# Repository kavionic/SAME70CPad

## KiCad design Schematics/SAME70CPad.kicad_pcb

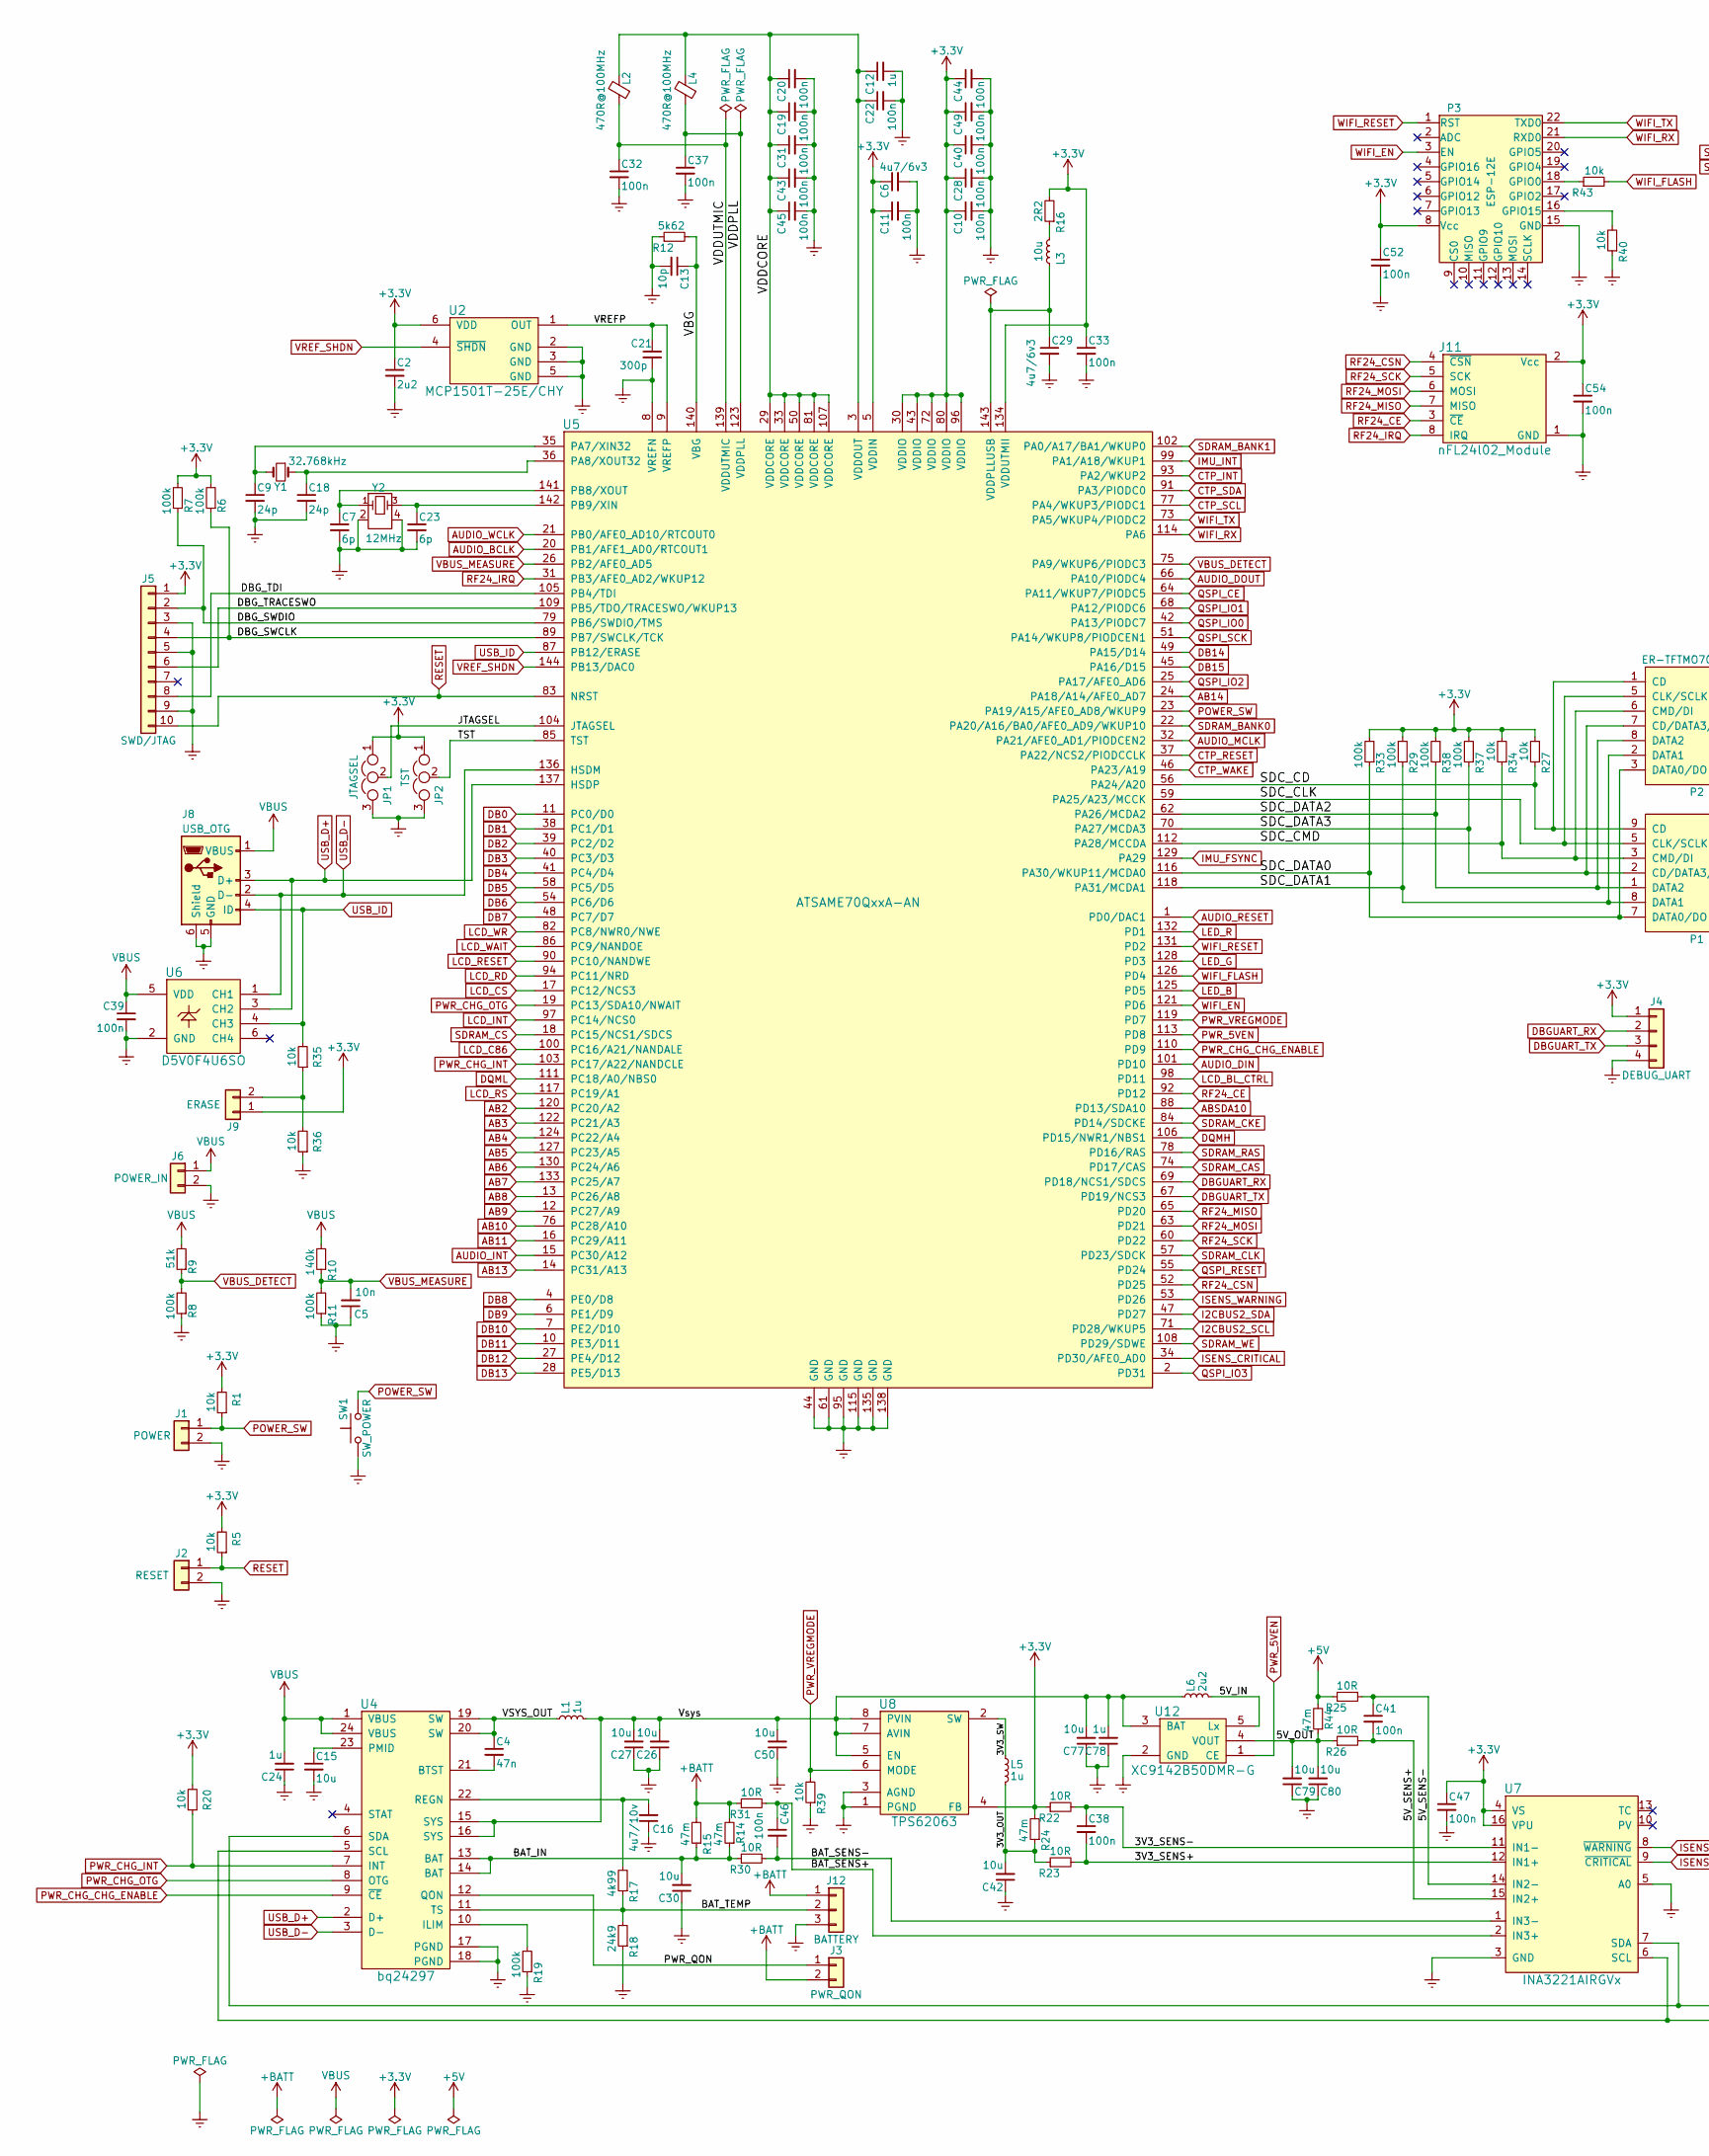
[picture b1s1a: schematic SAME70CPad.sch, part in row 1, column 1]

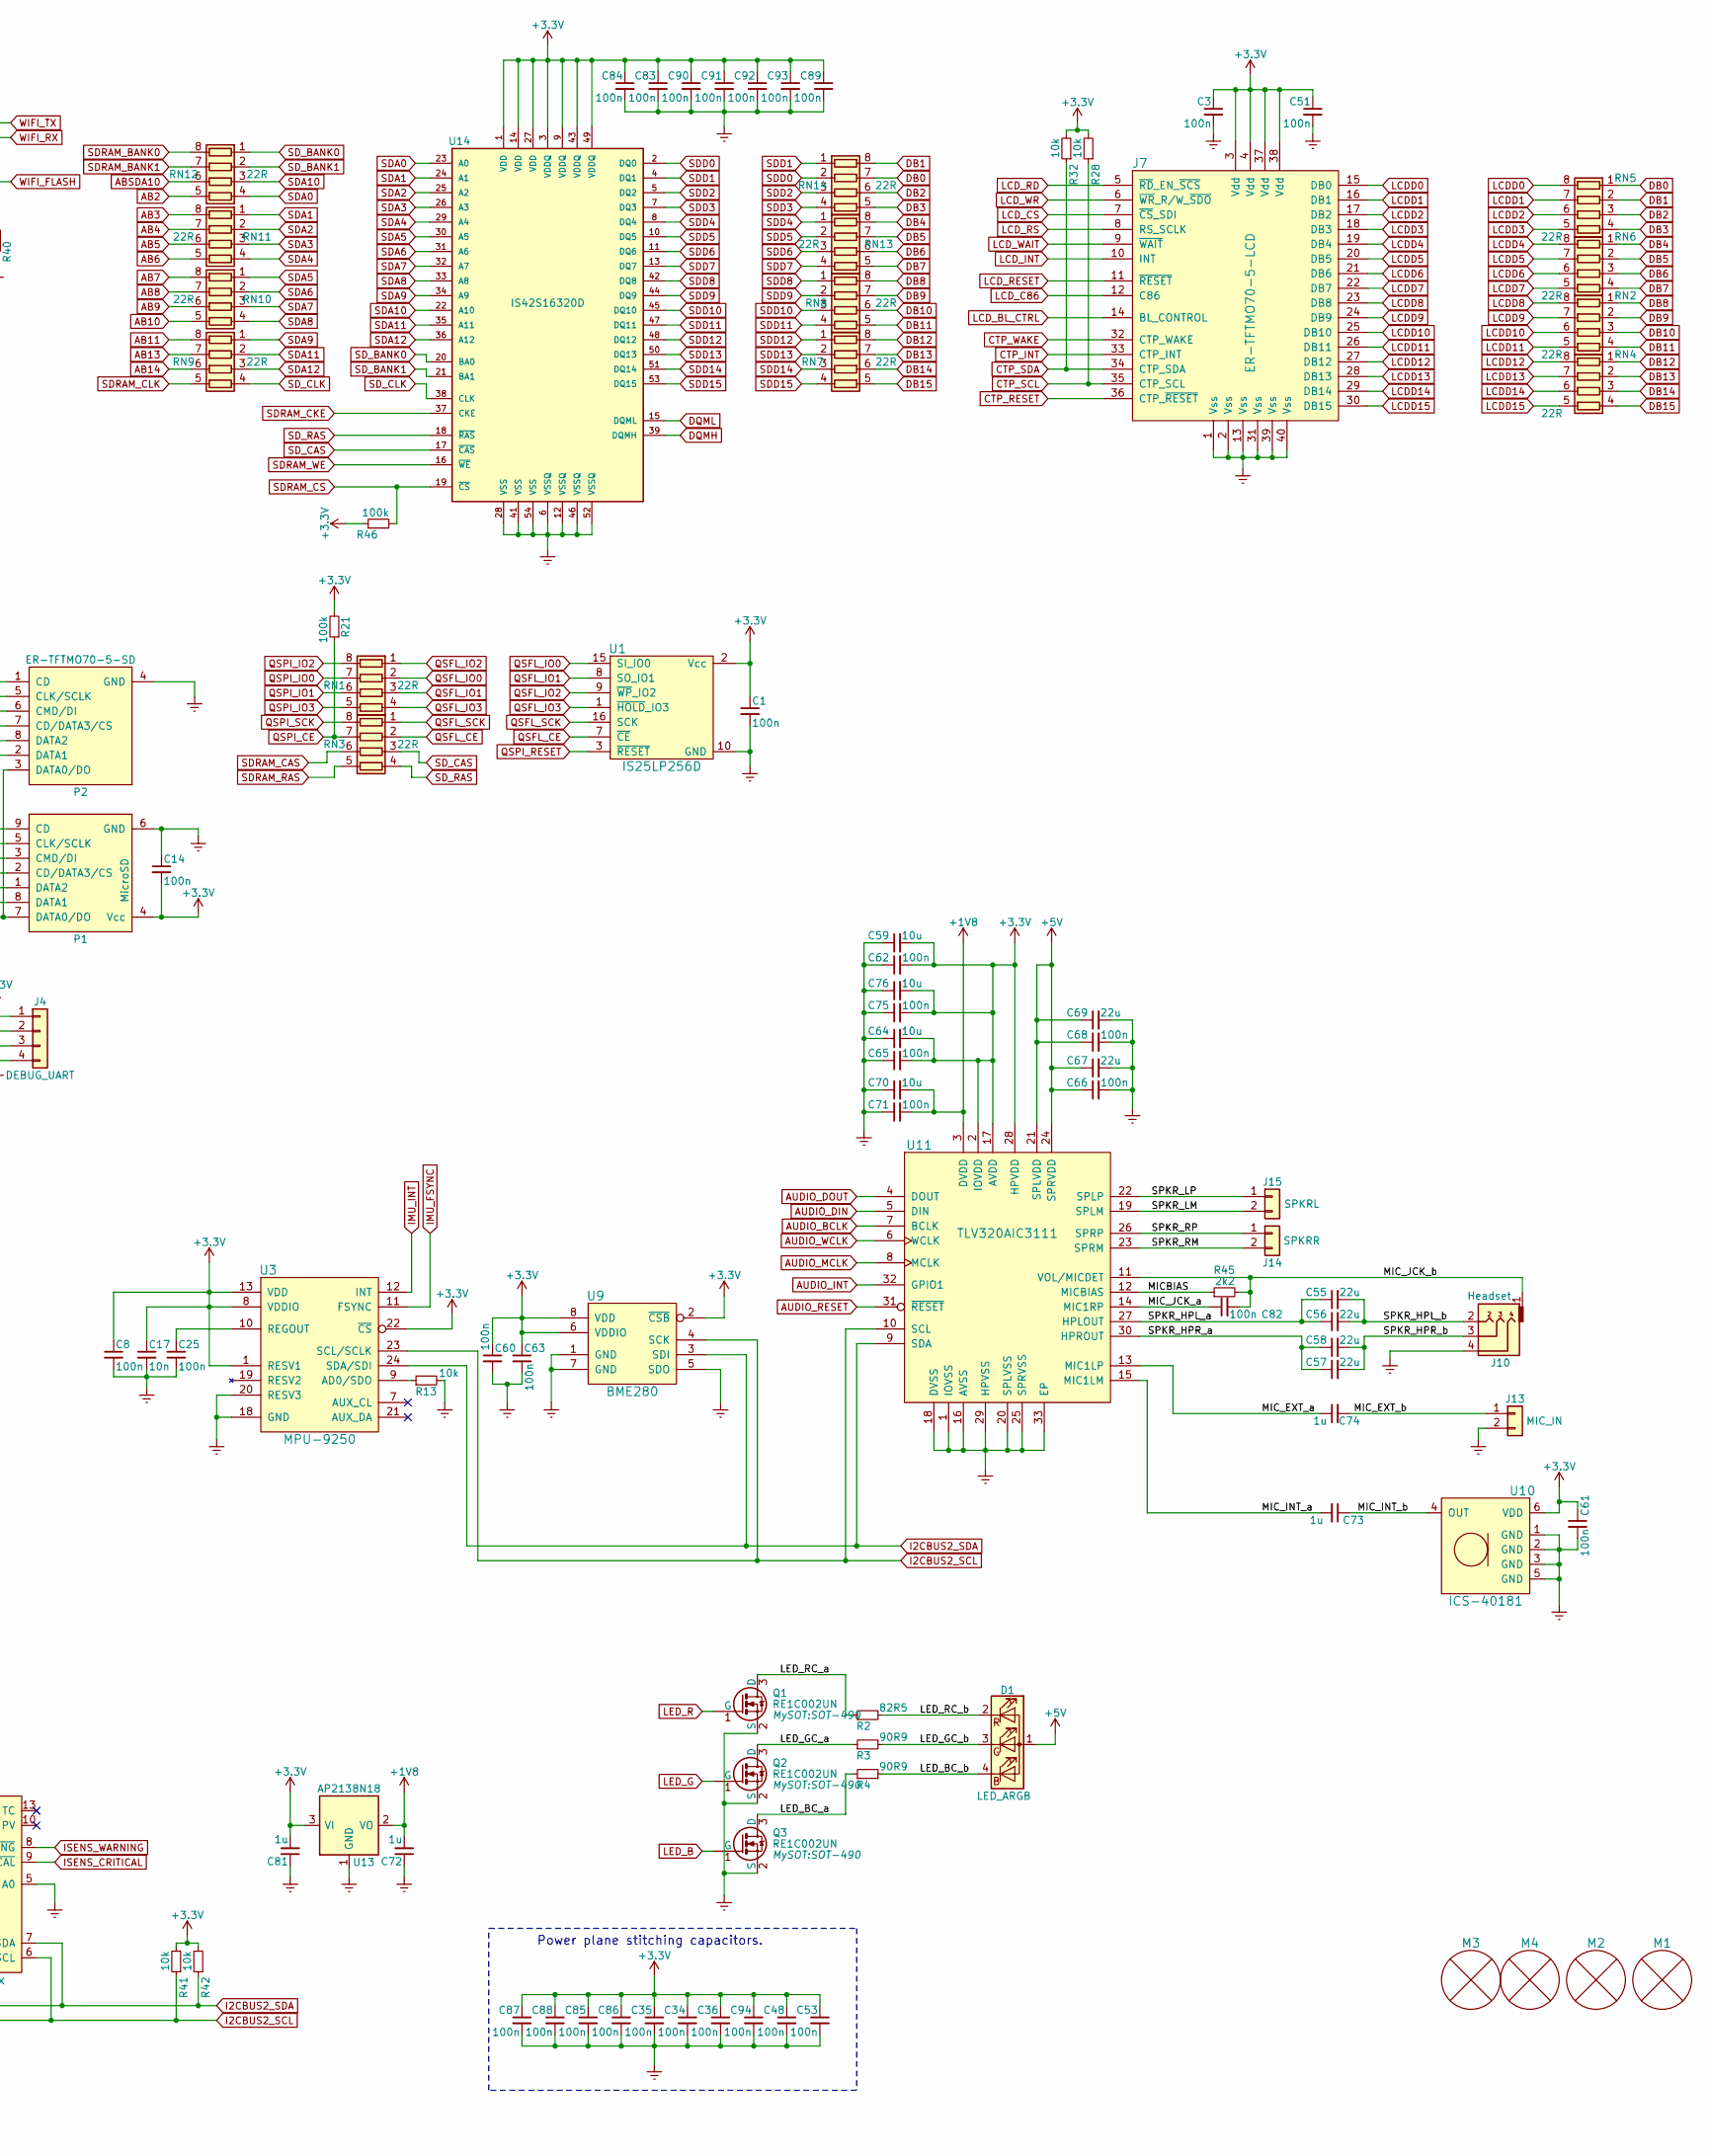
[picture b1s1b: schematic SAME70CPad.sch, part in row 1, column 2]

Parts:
C1, C3, C8, C10, C11, C14, C19, C20, C22, C25, C28, C31, C32, C33, C34, C35, C36, C37, C38, C39, C40, C41, C43, C44, C45, C46, C47, C48, C49, C51, C52, C53, C54, C60, C61, C62, C63, C65, C66, C68, C71, C75, C82, C83, C84, C85, C86, C87, C88, C89, C90, C91, C92, C93, C94: 100n; C_0603
C2: 2u2; C_0603
C4: 47n; C_0603
C5, C17: 10n; C_0603
C6, C29: 4u7/6v3; C_0603
C7, C23: 6p; C_0603
C9, C18: 24p; C_0603
C12, C24, C72, C73, C74, C78, C81: 1u; C_0603
C13: 10p; C_0603
C15, C26, C27, C30, C42, C50, C59, C64, C70, C76, C77, C79, C80: 10u; C_0805
C16: 4u7/10v; C_0805
C21: 300p; C_0603
C55, C56, C57, C58, C67, C69: 22u; C_1206
D1: LED_ARGB; PLCC4_3228
J1: POWER; JST_ZH_S2B-ZR_02x1.50mm_Angled
J2: RESET; JST_ZH_S2B-ZR_02x1.50mm_Angled
J3: PWR_QON; JST_ZH_S2B-ZR_02x1.50mm_Angled
J4: DEBUG_UART; JST_ZH_S4B-ZR_04x1.50mm_Angled
J5: SWD/JTAG; BoxHeader_Straight_2x05_Pitch1.27mm
J6: POWER_IN; JST_EH_S02B-EH_02x2.50mm_Angled
J7: ER-TFTMO70-5-LCD; ER-CON40HB-2
J8: USB_OTG; USB_Micro-B_Molex-105017-0001
J9: ERASE; PinHeader_1x02
J10: Headset; SJ2-3514A-SMT
J11: nFL24l02_Module; nFL24l02_module
J12: BATTERY; JST_EH_S03B-EH_03x2.50mm_Angled
J13: MIC_IN; JST_ZH_S2B-ZR_02x1.50mm_Angled
J14: SPKRL; JST_ZH_S2B-ZR_02x1.50mm_Angled
J15: SPKRR; JST_ZH_S2B-ZR_02x1.50mm_Angled
JP1: JTAGSEL; PinHeader_1x03
JP2: TST; PinHeader_1x03
L1, L5: 1u; L_2020
L2, L4: 470R@100MHz; Choke_SMD_0603_Standard
L3: 10u; L_0805
L6: 2u2; L_2020
M1, M2, M3, M4: MountingHole; MH7x3
P1: MicroSD
P2: ER-TFTMO70-5-SD; ER-CON08HB-2
P3: ESP-12E
Q1, Q2, Q3: RE1C002UN; SOT-490
R1, R5, R13, R20, R27, R28, R32, R34, R35, R36, R39, R40, R41, R42, R43: 10k; R_0603
R2: 82R5; R_0603
R3, R4: 90R9; R_0603
R6, R7, R8, R11, R19, R21, R29, R33, R37, R38, R46: 100k; R_0603
R9: 51k; R_0603
R10: 140k; R_0603
R12: 5k62; R_0603
R14, R15, R24, R44: 47m; R_0603
R16: 2R2; R_0603
R17: 4k99; R_0603
R18: 24k9; R_0603
R22, R23, R25, R26, R30, R31: 10R; R_0603
R45: 2k2; R_0603
RN1, RN2, RN3, RN4, RN5, RN6, RN7, RN8, RN9, RN10, RN11, RN12, RN13, RN14: 22R; R_0402x4
SW1: SW_POWER; TactSwitch_TH_RightAngle_6.3x7.5x7.1mm_5.85mm
U1: IS25LP256D; SOIC-16_7.5x10.3mm_Pitch1.27mm
U2: MCP1501T-25E/CHY; SOT-23-6
U3: MPU-9250; QFN-24_3x3mm_Pitch0.4mm
U4: bq24297; QFN-24-1EP_4x4mm_Pitch0.5mm
U5: ATSAME70QxxA-AN; TQFP-144_20x20mm_Pitch0.5mm
U6: D5V0F4U6SO; SOT-23-6
U7: INA3221AIRGVx; QFN-16-1EP_4x4mm_Pitch0.65mm
U8: TPS62063; WSON-8_0.5mm_Pitch
U9: BME280
U10: ICS-40181
U11: TLV320AIC3111; QFN-32-1EP_5x5mm_Pitch0.5mm
U12: XC9142B50DMR-G; SOT-25
U13: AP2138N18; SOT-23
U14: IS42S16320D; TSOP-54
Y1: 32.768kHz; Crystal_SMD_3215-2pin_3.2x1.5mm
Y2: 12MHz; Crystal-5032

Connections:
+1V8: C70.2, C71.2, C72.2, U11.3 (DVDD), U13.2 (VO)
+3V3: C1.1, C2.1, C3.1, C6.1, C8.1, C10.1, C11.1, C14.2, C17.1, C28.1, C33.1, C34.1, C35.1, C36.1, C40.1, C44.1, C47.1, C48.1, C49.1, C51.1, C52.1, C53.1, C54.1, C59.2, C60.1, C61.1, C62.2, C63.1, C64.2, C65.2, C75.2, C76.2, C81.2, C83.1, C84.1, C85.1, C86.1, C87.1, C88.1, C89.1, C90.1, C91.1, C92.1, C93.1, C94.1, J4.1, J5.1, J7.3 (Vdd), J7.4 (Vdd), J7.37 (Vdd), J7.38 (Vdd), J9.1, J11.2 (Vcc), JP1.1, JP2.1, P1.4 (Vcc), P3.8 (Vcc), R1.2, R5.2, R6.2, R7.2, R16.2, R20.2, R21.2, R22.1, R24.2, R27.2, R28.2, R29.2, R32.2, R33.2, R34.2, R37.2, R38.2, R41.2, R42.2, R46.1, U1.2 (Vcc), U2.6 (VDD), U3.1 (RESV1), U3.8 (VDDIO), U3.13 (VDD), U3.22 (~CS), U5.5 (VDDIN), U5.30 (VDDIO), U5.43 (VDDIO), U5.72 (VDDIO), U5.80 (VDDIO), U5.96 (VDDIO), U5.134 (VDDUTMII), U7.4 (VS), U7.16 (VPU), U8.4 (FB), U9.2 (~CSB), U9.6 (VDDIO), U9.8 (VDD), U10.6 (VDD), U11.2 (IOVDD), U11.17 (AVDD), U11.28 (HPVDD), U13.3 (VI), U14.1 (VDD), U14.3 (VDDQ), U14.9 (VDDQ), U14.14 (VDD), U14.27 (VDD), U14.43 (VDDQ), U14.49 (VDDQ)
+5V: C66.1, C67.1, C68.1, C69.1, D1.1 (A), R25.1, R44.2, U11.21 (SPLVDD), U11.24 (SPRVDD)
+BATT: J3.2, J12.1, R14.2, R15.2, R31.1
/3V3_OUT: C42.2, L5.2, R23.1, R24.1
/3V3_SENS+: C38.2, R23.2, U7.12 (IN1+)
/3V3_SENS-: C38.1, R22.2, U7.11 (IN1-)
/3V3_SW: L5.1, U8.2 (SW)
/5V_IN: L6.2, U12.5 (Lx)
/5V_OUT: C79.2, C80.2, R26.1, R44.1, U12.4 (VOUT)
/5V_SENS+: C41.2, R26.2, U7.15 (IN2+)
/5V_SENS-: C41.1, R25.2, U7.14 (IN2-)
/BAT_IN: C30.2, R14.1, R15.1, R30.1, U4.13 (BAT), U4.14 (BAT)
/BAT_SENS+: C46.1, R31.2, U7.2 (IN3+)
/BAT_SENS-: C46.2, R30.2, U7.1 (IN3-)
/BAT_TEMP: J12.2, R17.1, R18.2, U4.11 (TS)
/DBG_SWCLK: J5.4, R6.1, U5.89 (PB7/SWCLK/TCK)
/DBG_SWDIO: J5.2, R7.1, U5.79 (PB6/SWDIO/TMS)
/DBG_TDI: J5.8, U5.105 (PB4/TDI)
/DBG_TRACESWO: J5.6, U5.109 (PB5/TDO/TRACESWO/WKUP13)
/JTAGSEL: JP1.2, U5.104 (JTAGSEL)
/LED_BC_a: Q3.3 (D), R4.1
/LED_BC_b: D1.4 (BK), R4.2
/LED_GC_a: Q2.3 (D), R3.1
/LED_GC_b: D1.3 (GK), R3.2
/LED_RC_a: Q1.3 (D), R2.1
/LED_RC_b: D1.2 (RK), R2.2
/MICBIAS: R45.1, U11.12 (MICBIAS)
/MIC_EXT_a: C74.1, U11.13 (MIC1LP)
/MIC_EXT_b: C74.2, J13.1
/MIC_INT_a: C73.2, U11.15 (MIC1LM)
/MIC_INT_b: C73.1, U10.4 (OUT)
/MIC_JCK_a: C82.1, U11.14 (MIC1RP)
/MIC_JCK_b: C82.2, J10.1, R45.2, U11.11 (VOL/MICDET)
/PWR_QON: J3.1, U4.12 (QON)
/SDC_CD: P1.9 (CD), P2.1 (CD), R27.1, U5.56 (PA24/A20)
/SDC_CLK: P1.5 (CLK/SCLK), P2.5 (CLK/SCLK), U5.59 (PA25/A23/MCCK)
/SDC_CMD: P1.3 (CMD/DI), P2.6 (CMD/DI), R34.1, U5.112 (PA28/MCCDA)
/SDC_DATA0: P1.7 (DATA0/DO), P2.3 (DATA0/DO), R33.1, U5.116 (PA30/WKUP11/MCDA0)
/SDC_DATA1: P1.8 (DATA1), P2.2 (DATA1), R29.1, U5.118 (PA31/MCDA1)
/SDC_DATA2: P1.1 (DATA2), P2.8 (DATA2), R38.1, U5.62 (PA26/MCDA2)
/SDC_DATA3: P1.2 (CD/DATA3/CS), P2.7 (CD/DATA3/CS), R37.1, U5.70 (PA27/MCDA3)
/SPKR_HPL_a: C55.1, C56.1, U11.27 (HPLOUT)
/SPKR_HPL_b: C55.2, C56.2, J10.2
/SPKR_HPR_a: C57.1, C58.1, U11.30 (HPROUT)
/SPKR_HPR_b: C57.2, C58.2, J10.3
/SPKR_LM: J14.2, U11.19 (SPLM)
/SPKR_LP: J14.1, U11.22 (SPLP)
/SPKR_RM: J15.2, U11.23 (SPRM)
/SPKR_RP: J15.1, U11.26 (SPRP)
/TST: JP2.2, U5.85 (TST)
/VBG: C13.1, R12.2, U5.140 (VBG)
/VDDCORE: C12.1, C19.1, C20.1, C22.1, C31.1, C43.1, C45.1, L2.2, L4.2, U5.3 (VDDOUT), U5.29 (VDDCORE), U5.33 (VDDCORE), U5.50 (VDDCORE), U5.81 (VDDCORE), U5.107 (VDDCORE)
/VDDPLL: C37.1, L4.1, U5.123 (VDDPLL)
/VDDUTMIC: C32.1, L2.1, U5.139 (VDDUTMIC)
/VREFP: C21.1, U2.1 (OUT), U5.9 (VREFP)
/VSYS_OUT: C4.1, L1.1, U4.19 (SW), U4.20 (SW)
/Vsys: C26.2, C27.2, C50.2, C77.2, C78.2, L1.2, L6.1, U4.15 (SYS), U4.16 (SYS), U8.5 (EN), U8.7 (AVIN), U8.8 (PVIN), U12.3 (BAT)
AB2: RN12.5 (R4.2), U5.120 (PC20/A2)
AB3: RN11.8 (R1.2), U5.122 (PC21/A3)
AB4: RN11.7 (R2.2), U5.124 (PC22/A4)
AB5: RN11.6 (R3.2), U5.127 (PC23/A5)
AB6: RN11.5 (R4.2), U5.130 (PC24/A6)
AB7: RN10.8 (R1.2), U5.133 (PC25/A7)
AB8: RN10.7 (R2.2), U5.13 (PC26/A8)
AB9: RN10.6 (R3.2), U5.12 (PC27/A9)
AB10: RN10.5 (R4.2), U5.76 (PC28/A10)
AB11: RN9.8 (R1.2), U5.16 (PC29/A11)
AB13: RN9.7 (R2.2), U5.14 (PC31/A13)
AB14: RN9.6 (R3.2), U5.24 (PA18/A14/AFE0_AD7)
ABSDA10: RN12.6 (R3.2), U5.88 (PD13/SDA10)
AUDIO_BCLK: U5.20 (PB1/AFE1_AD0/RTCOUT1), U11.7 (BCLK)
AUDIO_DIN: U5.101 (PD10), U11.5 (DIN)
AUDIO_DOUT: U5.66 (PA10/PIODC4), U11.4 (DOUT)
AUDIO_INT: U5.15 (PC30/A12), U11.32 (GPIO1)
AUDIO_MCLK: U5.32 (PA21/AFE0_AD1/PIODCEN2), U11.8 (MCLK)
AUDIO_RESET: U5.1 (PD0/DAC1), U11.31 (~RESET)
AUDIO_WCLK: U5.21 (PB0/AFE0_AD10/RTCOUT0), U11.6 (WCLK)
CTP_INT: J7.33 (CTP_INT), U5.93 (PA2/WKUP2)
CTP_RESET: J7.36 (CTP_~RESET), U5.37 (PA22/NCS2/PIODCCLK)
CTP_SCL: J7.35 (CTP_SCL), R28.1, U5.77 (PA4/WKUP3/PIODC1)
CTP_SDA: J7.34 (CTP_SDA), R32.1, U5.91 (PA3/PIODC0)
CTP_WAKE: J7.32 (CTP_WAKE), U5.46 (PA23/A19)
DB0: RN5.1 (R1.1), RN14.7 (R2.2), U5.11 (PC0/D0)
DB1: RN5.2 (R2.1), RN14.8 (R1.2), U5.38 (PC1/D1)
DB2: RN5.3 (R3.1), RN14.6 (R3.2), U5.39 (PC2/D2)
DB3: RN5.4 (R4.1), RN14.5 (R4.2), U5.40 (PC3/D3)
DB4: RN6.1 (R1.1), RN13.8 (R1.2), U5.41 (PC4/D4)
DB5: RN6.2 (R2.1), RN13.7 (R2.2), U5.58 (PC5/D5)
DB6: RN6.3 (R3.1), RN13.6 (R3.2), U5.54 (PC6/D6)
DB7: RN6.4 (R4.1), RN13.5 (R4.2), U5.48 (PC7/D7)
DB8: RN2.1 (R1.1), RN8.8 (R1.2), U5.4 (PE0/D8)
DB9: RN2.2 (R2.1), RN8.7 (R2.2), U5.6 (PE1/D9)
DB10: RN2.3 (R3.1), RN8.6 (R3.2), U5.7 (PE2/D10)
DB11: RN2.4 (R4.1), RN8.5 (R4.2), U5.10 (PE3/D11)
DB12: RN4.1 (R1.1), RN7.8 (R1.2), U5.27 (PE4/D12)
DB13: RN4.2 (R2.1), RN7.7 (R2.2), U5.28 (PE5/D13)
DB14: RN4.3 (R3.1), RN7.6 (R3.2), U5.49 (PA15/D14)
DB15: RN4.4 (R4.1), RN7.5 (R4.2), U5.45 (PA16/D15)
DBGUART_RX: J4.2, U5.69 (PD18/NCS1/SDCS)
DBGUART_TX: J4.3, U5.67 (PD19/NCS3)
DQMH: U5.106 (PD15/NWR1/NBS1), U14.39 (DQMH)
DQML: U5.111 (PC18/A0/NBS0), U14.15 (DQML)
Earth: C1.2, C2.2, C3.2, C5.1, C6.2, C7.2, C8.2, C9.2, C10.2, C11.2, C12.2, C13.2, C14.1, C15.2, C16.1, C17.2, C18.2, C19.2, C20.2, C21.2, C22.2, C23.2, C24.1, C25.2, C26.1, C27.1, C28.2, C29.2, C30.1, C31.2, C32.2, C33.2, C34.2, C35.2, C36.2, C37.2, C39.2, C40.2, C42.1, C43.2, C44.2, C45.2, C47.2, C48.2, C49.2, C50.1, C51.2, C52.2, C53.2, C54.2, C59.1, C60.2, C61.2, C62.1, C63.2, C64.1, C65.1, C66.2, C67.2, C68.2, C69.2, C70.1, C71.1, C72.1, C75.1, C76.1, C77.1, C78.1, C79.1, C80.1, C81.1, C83.2, C84.2, C85.2, C86.2, C87.2, C88.2, C89.2, C90.2, C91.2, C92.2, C93.2, C94.2, J1.2, J2.2, J4.4, J5.3, J5.5, J5.9, J6.2, J7.1 (Vss), J7.2 (Vss), J7.13 (Vss), J7.31 (Vss), J7.39 (Vss), J7.40 (Vss), J8.5 (GND), J8.6 (Shield), J10.4, J11.1 (GND), J12.3, J13.2, JP1.3, JP2.3, P1.6 (GND), P1.10 (GND), P1.11 (GND), P1.12 (GND), P1.13 (GND), P2.4 (GND), P3.15 (GND), Q1.2 (S), Q2.2 (S), Q3.2 (S), R8.1, R11.1, R12.1, R13.2, R18.1, R19.1, R36.1, R39.1, R40.1, SW1.1, U1.10 (GND), U2.2 (GND), U2.3 (GND), U2.5 (GND), U3.18 (GND), U3.20 (RESV3), U4.17 (PGND), U4.18 (PGND), U4.25 (PGND), U5.8 (VREFN), U5.44 (GND), U5.61 (GND), U5.95 (GND), U5.115 (GND), U5.135 (GND), U5.138 (GND), U6.2 (GND), U7.3 (GND), U7.5 (A0), U7.17 (GND), U8.1 (PGND), U8.3 (AGND), U8.9 (PGND), U9.1 (GND), U9.5 (SDO), U9.7 (GND), U10.1 (GND), U10.2 (GND), U10.3 (GND), U10.5 (GND), U11.1 (IOVSS), U11.16 (AVSS), U11.18 (DVSS), U11.20 (SPLVSS), U11.25 (SPRVSS), U11.29 (HPVSS), U11.33 (EP), U12.2 (GND), U13.1 (GND), U14.6 (VSSQ), U14.12 (VSSQ), U14.28 (VSS), U14.41 (VSS), U14.46 (VSSQ), U14.52 (VSSQ), U14.54 (VSS), Y2.2 (NC), Y2.4 (NC)
I2CBUS2_SCL: R41.1, U3.23 (SCL/SCLK), U4.5 (SCL), U5.71 (PD28/WKUP5), U7.6 (SCL), U9.4 (SCK), U11.10 (SCL)
I2CBUS2_SDA: R42.1, U3.24 (SDA/SDI), U4.6 (SDA), U5.47 (PD27), U7.7 (SDA), U9.3 (SDI), U11.9 (SDA)
IMU_FSYNC: U3.11 (FSYNC), U5.129 (PA29)
IMU_INT: U3.12 (INT), U5.99 (PA1/A18/WKUP1)
ISENS_CRITICAL: U5.34 (PD30/AFE0_AD0), U7.9 (~CRITICAL)
ISENS_WARNING: U5.53 (PD26), U7.8 (~WARNING)
LCDD0: J7.15 (DB0), RN5.8 (R1.2)
LCDD1: J7.16 (DB1), RN5.7 (R2.2)
LCDD2: J7.17 (DB2), RN5.6 (R3.2)
LCDD3: J7.18 (DB3), RN5.5 (R4.2)
LCDD4: J7.19 (DB4), RN6.8 (R1.2)
LCDD5: J7.20 (DB5), RN6.7 (R2.2)
LCDD6: J7.21 (DB6), RN6.6 (R3.2)
LCDD7: J7.22 (DB7), RN6.5 (R4.2)
LCDD8: J7.23 (DB8), RN2.8 (R1.2)
LCDD9: J7.24 (DB9), RN2.7 (R2.2)
LCDD10: J7.25 (DB10), RN2.6 (R3.2)
LCDD11: J7.26 (DB11), RN2.5 (R4.2)
LCDD12: J7.27 (DB12), RN4.8 (R1.2)
LCDD13: J7.28 (DB13), RN4.7 (R2.2)
LCDD14: J7.29 (DB14), RN4.6 (R3.2)
LCDD15: J7.30 (DB15), RN4.5 (R4.2)
LCD_BL_CTRL: J7.14 (BL_CONTROL), U5.98 (PD11)
LCD_C86: J7.12 (C86), U5.100 (PC16/A21/NANDALE)
LCD_CS: J7.7 (~CS~_SDI), U5.17 (PC12/NCS3)
LCD_INT: J7.10 (INT), U5.97 (PC14/NCS0)
LCD_RD: J7.5 (~RD~_EN_~SCS), U5.94 (PC11/NRD)
LCD_RESET: J7.11 (~RESET), U5.90 (PC10/NANDWE)
LCD_RS: J7.8 (RS_SCLK), U5.117 (PC19/A1)
LCD_WAIT: J7.9 (~WAIT), U5.86 (PC9/NANDOE)
LCD_WR: J7.6 (~WR~_R/W_~SDO), U5.82 (PC8/NWR0/NWE)
LED_B: Q3.1 (G), U5.125 (PD5)
LED_G: Q2.1 (G), U5.128 (PD3)
LED_R: Q1.1 (G), U5.132 (PD1)
unnamed: C4.2, U4.21 (BTST)
unnamed: C7.1, U5.141 (PB8/XOUT), Y2.1 (X1)
unnamed: C9.1, U5.35 (PA7/XIN32), Y1.2
unnamed: C15.1, U4.23 (PMID)
unnamed: C16.2, R17.2, U4.22 (REGN)
unnamed: C18.1, U5.36 (PA8/XOUT32), Y1.1
unnamed: C23.1, U5.142 (PB9/XIN), Y2.3 (X2)
unnamed: C25.1, U3.10 (REGOUT)
unnamed: C29.1, L3.1, U5.143 (VDDPLLUSB)
unnamed: J9.2, R35.1, R36.2
unnamed: L3.2, R16.1
unnamed: P3.16 (GPIO15), R40.2
unnamed: P3.18 (GPIO0), R43.1
unnamed: R13.1, U3.9 (AD0/SDO)
unnamed: R19.2, U4.10 (ILIM)
POWER_SW: J1.1, R1.1, SW1.2, U5.23 (PA19/A15/AFE0_AD8/WKUP9)
PWR_5VEN: U5.113 (PD8), U12.1 (CE)
PWR_CHG_CHG_ENABLE: U4.9 (~CE), U5.110 (PD9)
PWR_CHG_INT: R20.1, U4.7 (INT), U5.103 (PC17/A22/NANDCLE)
PWR_CHG_OTG: U4.8 (OTG), U5.19 (PC13/SDA10/NWAIT)
PWR_VREGMODE: R39.2, U5.119 (PD7), U8.6 (MODE)
QSFL_CE: RN3.2 (R2.1), U1.7 (~CE)
QSFL_IO0: RN1.2 (R2.1), U1.15 (SI_IO0)
QSFL_IO1: RN1.3 (R3.1), U1.8 (SO_IO1)
QSFL_IO2: RN1.1 (R1.1), U1.9 (~WP~_IO2)
QSFL_IO3: RN1.4 (R4.1), U1.1 (~HOLD~_IO3)
QSFL_SCK: RN3.1 (R1.1), U1.16 (SCK)
QSPI_CE: R21.1, RN3.7 (R2.2), U5.64 (PA11/WKUP7/PIODC5)
QSPI_IO0: RN1.7 (R2.2), U5.42 (PA13/PIODC7)
QSPI_IO1: RN1.6 (R3.2), U5.68 (PA12/PIODC6)
QSPI_IO2: RN1.8 (R1.2), U5.25 (PA17/AFE0_AD6)
QSPI_IO3: RN1.5 (R4.2), U5.2 (PD31)
QSPI_RESET: U1.3 (~RESET), U5.55 (PD24)
QSPI_SCK: RN3.8 (R1.2), U5.51 (PA14/WKUP8/PIODCEN1)
RESET: J2.1, J5.10, R5.1, U5.83 (NRST)
RF24_CE: J11.3 (~CE), U5.92 (PD12)
RF24_CSN: J11.4 (~CSN), U5.52 (PD25)
RF24_IRQ: J11.8 (IRQ), U5.31 (PB3/AFE0_AD2/WKUP12)
RF24_MISO: J11.7 (MISO), U5.65 (PD20)
RF24_MOSI: J11.6 (MOSI), U5.63 (PD21)
RF24_SCK: J11.5 (SCK), U5.60 (PD22)
SDA0: RN12.4 (R4.1), U14.23 (A0)
SDA1: RN11.1 (R1.1), U14.24 (A1)
SDA2: RN11.2 (R2.1), U14.25 (A2)
SDA3: RN11.3 (R3.1), U14.26 (A3)
SDA4: RN11.4 (R4.1), U14.29 (A4)
SDA5: RN10.1 (R1.1), U14.30 (A5)
SDA6: RN10.2 (R2.1), U14.31 (A6)
SDA7: RN10.3 (R3.1), U14.32 (A7)
SDA8: RN10.4 (R4.1), U14.33 (A8)
SDA9: RN9.1 (R1.1), U14.34 (A9)
SDA10: RN12.3 (R3.1), U14.22 (A10)
SDA11: RN9.2 (R2.1), U14.35 (A11)
SDA12: RN9.3 (R3.1), U14.36 (A12)
SDD0: RN14.2 (R2.1), U14.2 (DQ0)
SDD1: RN14.1 (R1.1), U14.4 (DQ1)
SDD2: RN14.3 (R3.1), U14.5 (DQ2)
SDD3: RN14.4 (R4.1), U14.7 (DQ3)
SDD4: RN13.1 (R1.1), U14.8 (DQ4)
SDD5: RN13.2 (R2.1), U14.10 (DQ5)
SDD6: RN13.3 (R3.1), U14.11 (DQ6)
SDD7: RN13.4 (R4.1), U14.13 (DQ7)
SDD8: RN8.1 (R1.1), U14.42 (DQ8)
SDD9: RN8.2 (R2.1), U14.44 (DQ9)
SDD10: RN8.3 (R3.1), U14.45 (DQ10)
SDD11: RN8.4 (R4.1), U14.47 (DQ11)
SDD12: RN7.1 (R1.1), U14.48 (DQ12)
SDD13: RN7.2 (R2.1), U14.50 (DQ13)
SDD14: RN7.3 (R3.1), U14.51 (DQ14)
SDD15: RN7.4 (R4.1), U14.53 (DQ15)
SDRAM_BANK0: RN12.8 (R1.2), U5.22 (PA20/A16/BA0/AFE0_AD9/WKUP10)
SDRAM_BANK1: RN12.7 (R2.2), U5.102 (PA0/A17/BA1/WKUP0)
SDRAM_CAS: RN3.6 (R3.2), U5.74 (PD17/CAS)
SDRAM_CKE: U5.84 (PD14/SDCKE), U14.37 (CKE)
SDRAM_CLK: RN9.5 (R4.2), U5.57 (PD23/SDCK)
SDRAM_CS: R46.2, U5.18 (PC15/NCS1/SDCS), U14.19 (~CS~)
SDRAM_RAS: RN3.5 (R4.2), U5.78 (PD16/RAS)
SDRAM_WE: U5.108 (PD29/SDWE), U14.16 (~WE~)
SD_BANK0: RN12.1 (R1.1), U14.20 (BA0)
SD_BANK1: RN12.2 (R2.1), U14.21 (BA1)
SD_CAS: RN3.3 (R3.1), U14.17 (~CAS~)
SD_CLK: RN9.4 (R4.1), U14.38 (CLK)
SD_RAS: RN3.4 (R4.1), U14.18 (~RAS~)
USB_D+: J8.3 (D+), U4.2 (D+), U5.137 (HSDP), U6.3 (CH2)
USB_D-: J8.2 (D-), U4.3 (D-), U5.136 (HSDM), U6.1 (CH1)
USB_ID: J8.4 (ID), R35.2, U5.87 (PB12/ERASE), U6.4 (CH3)
VBUS: C24.2, C39.1, J6.1, J8.1 (VBUS), R9.2, R10.2, U4.1 (VBUS), U4.24 (VBUS), U6.5 (VDD)
VBUS_DETECT: R8.2, R9.1, U5.75 (PA9/WKUP6/PIODC3)
VBUS_MEASURE: C5.2, R10.1, R11.2, U5.26 (PB2/AFE0_AD5)
VREF_SHDN: U2.4 (~SHDN), U5.144 (PB13/DAC0)
WIFI_EN: P3.3 (EN), U5.121 (PD6)
WIFI_FLASH: R43.2, U5.126 (PD4)
WIFI_RESET: P3.1 (RST), U5.131 (PD2)
WIFI_RX: P3.21 (RXD0), U5.114 (PA6)
WIFI_TX: P3.22 (TXD0), U5.73 (PA5/WKUP4/PIODC2)

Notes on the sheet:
Power plane stitching capacitors.

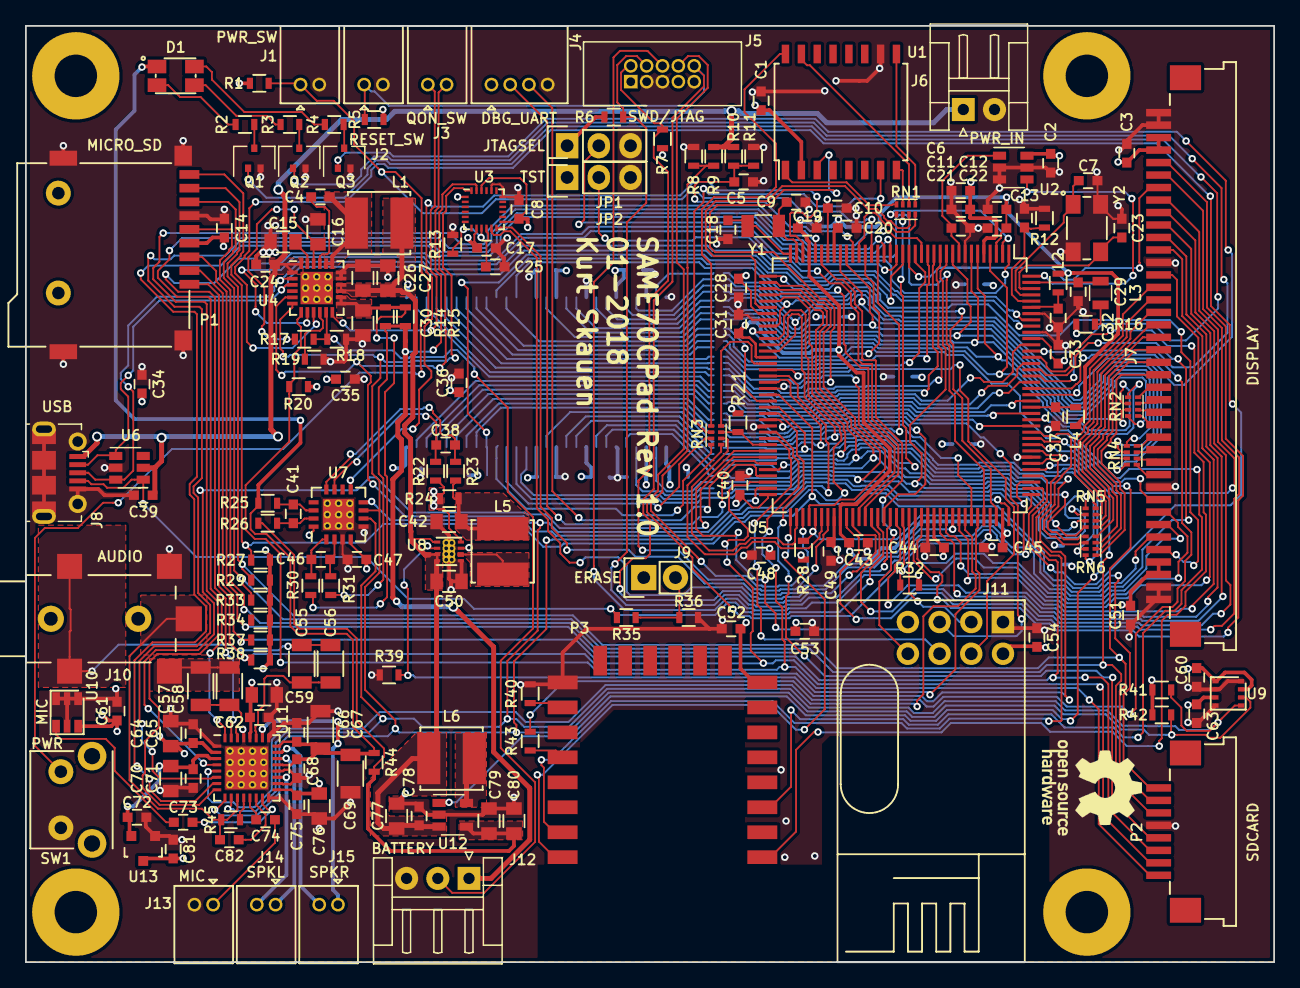
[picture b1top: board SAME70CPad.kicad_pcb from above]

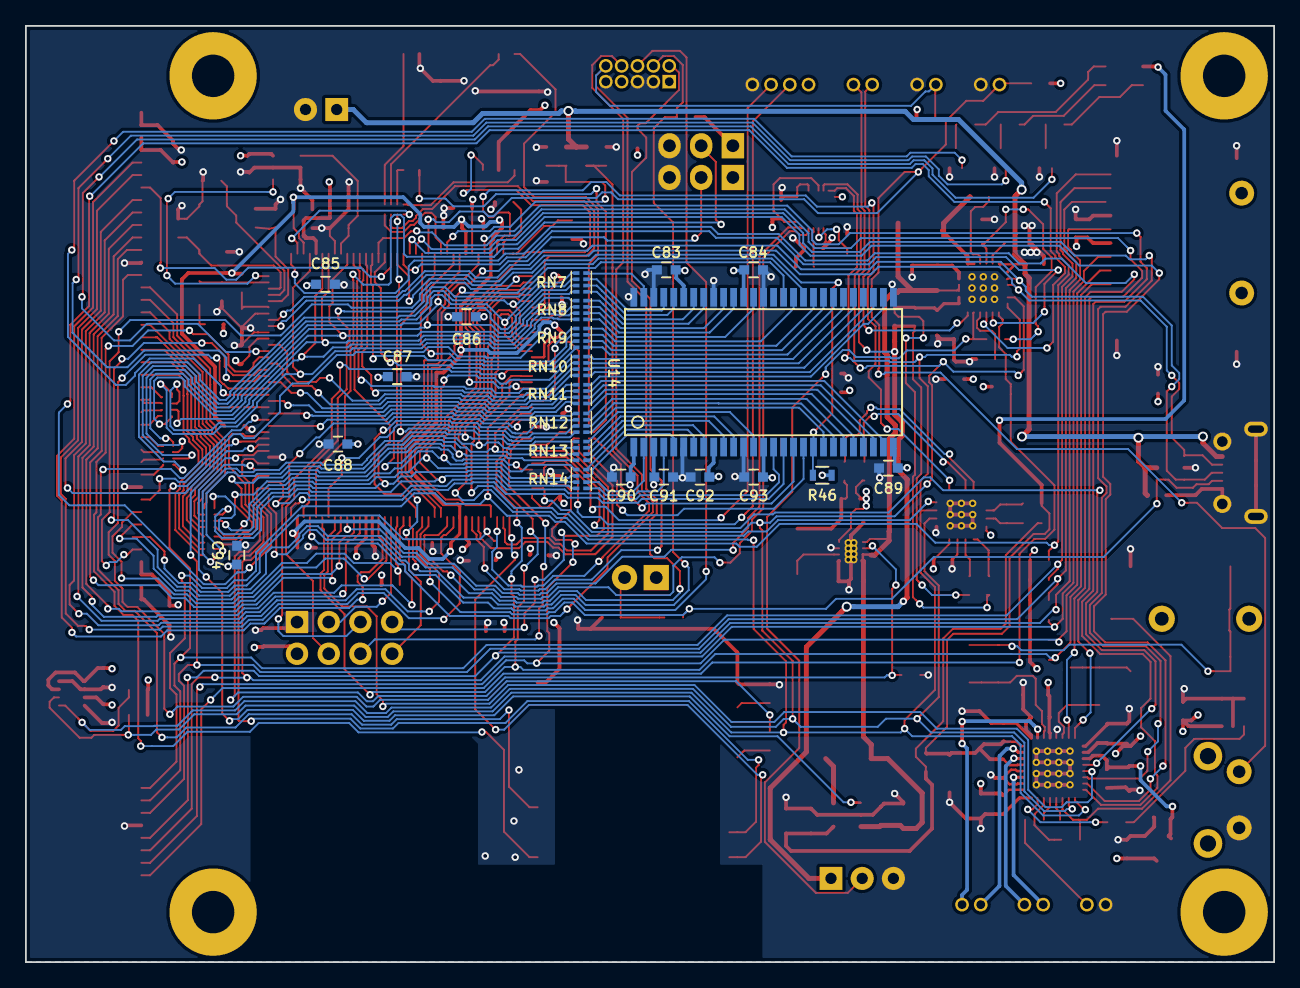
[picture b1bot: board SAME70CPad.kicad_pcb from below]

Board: 4 copper layers, 100.0 x 75.0 mm, 205 parts (22 on the bottom side), 233 nets.

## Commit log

2018-01-12 :boom::camel: Added .gitattributes & .gitignore files
2018-01-12 Initial version of SAME70CPad.
2018-01-13 Added some missing pullup resistors plus misc cleanup and optimization of the layout.
2018-01-13 - Annotated components geographically from the PCB layout. - Added the OSHW logo to the PCB. - Some minor layout cleanup.
